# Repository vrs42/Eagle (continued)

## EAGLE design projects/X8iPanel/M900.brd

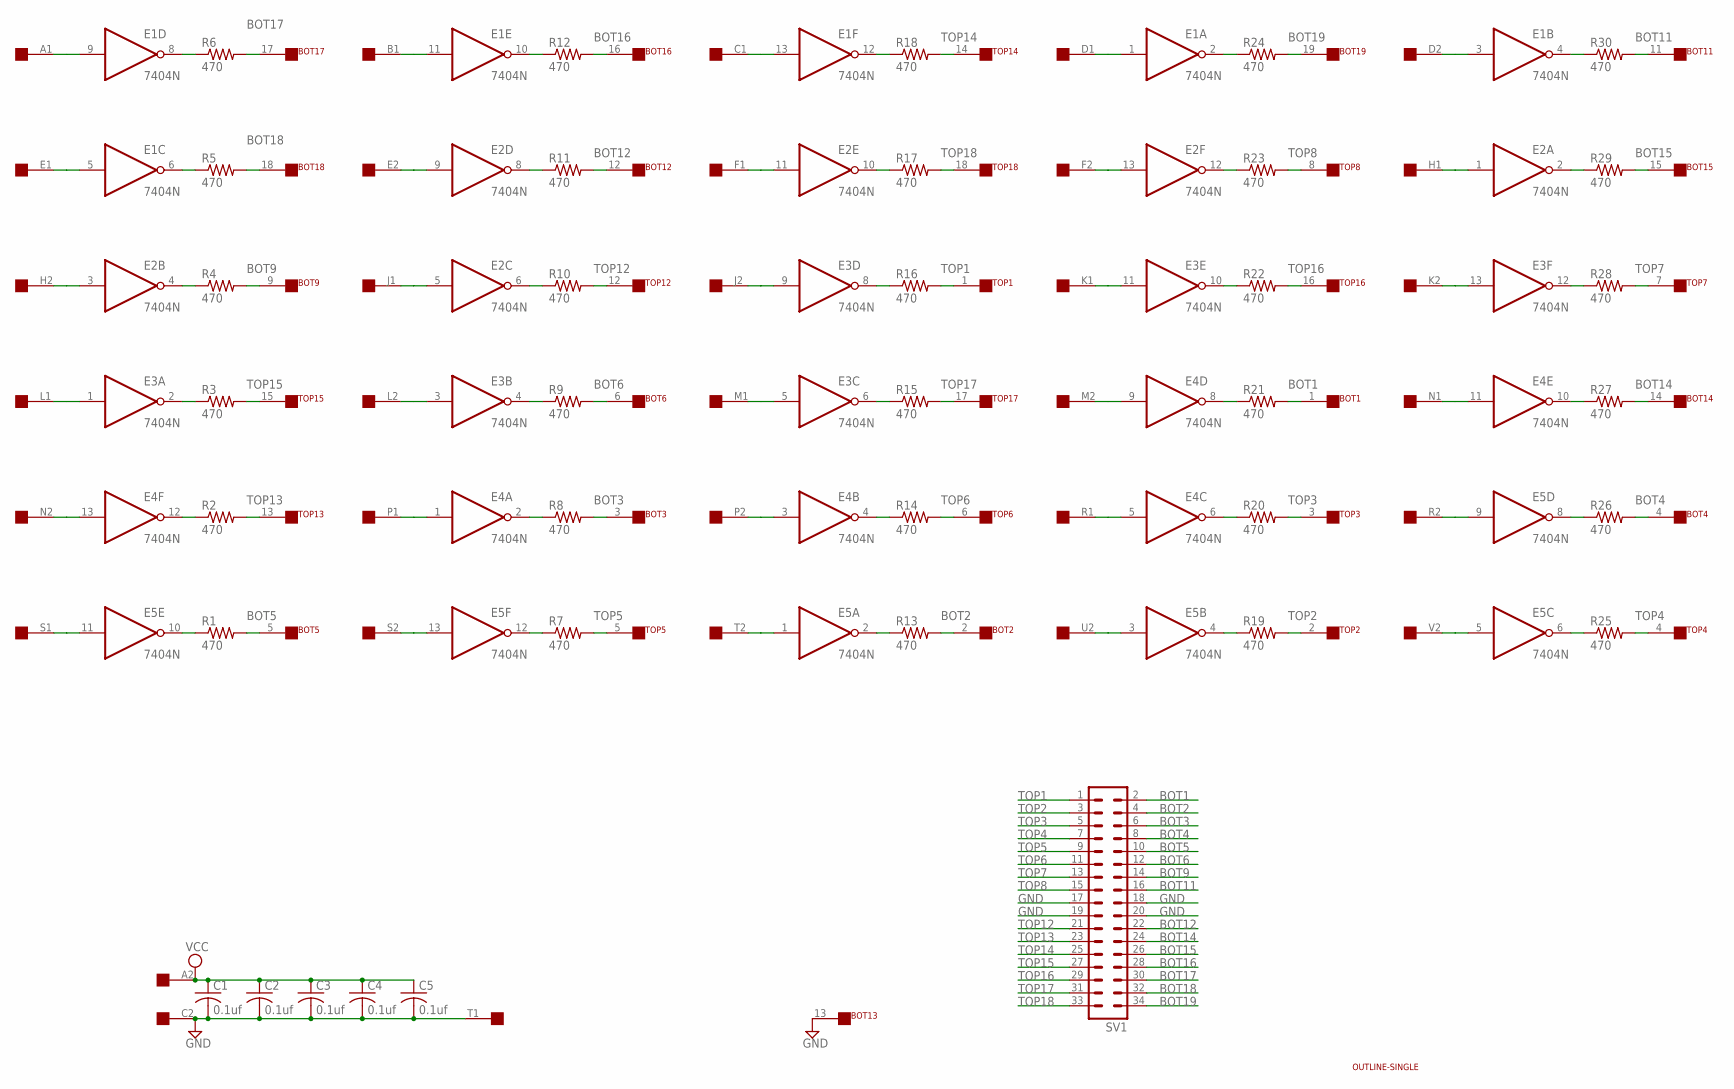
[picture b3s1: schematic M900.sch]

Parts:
BOT: FLEX19
C1, C2, C3, C4, C5: 0.1uf; C050-025X075
E1, E2, E3, E4, E5: 7404N; DIL14
EDGE: SINGLE; EDGE-CON2
R1, R2, R3, R4, R5, R6, R7, R8, R9, R10, R11, R12, R13, R14, R15, R16, R17, R18, R19, R20, R21, R22, R23, R24, R25, R26, R27, R28, R29, R30: 470; 0207/10
SV1: MA17-2
TOP: FLEX19
U$2: OUTLINE-SINGLE; SINGLE

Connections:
BOT1: BOT.1, R21.2, SV1.2
BOT2: BOT.2, R13.2, SV1.4
BOT3: BOT.3, R8.2, SV1.6
BOT4: BOT.4, R26.2, SV1.8
BOT5: BOT.5, R1.2, SV1.10
BOT6: BOT.6, R9.2, SV1.12
BOT9: BOT.9, R4.2, SV1.14
BOT11: BOT.11, R30.2, SV1.16
BOT12: BOT.12, R11.2, SV1.22
BOT14: BOT.14, R27.2, SV1.24
BOT15: BOT.15, R29.2, SV1.26
BOT16: BOT.16, R12.2, SV1.28
BOT17: BOT.17, R6.2, SV1.30
BOT18: BOT.18, R5.2, SV1.32
BOT19: BOT.19, R24.2, SV1.34
GND: BOT.13, C1.2, C2.2, C3.2, C4.2, C5.2, E1.7 (GND), E2.7 (GND), E3.7 (GND), E4.7 (GND), E5.7 (GND), EDGE.C2, EDGE.T1, SV1.17, SV1.18, SV1.19, SV1.20
unnamed: E1.9 (I), EDGE.A1
unnamed: E1.8 (O), R6.1
unnamed: E1.6 (O), R5.1
unnamed: E2.4 (O), R4.1
unnamed: E3.2 (O), R3.1
unnamed: E4.12 (O), R2.1
unnamed: E2.3 (I), EDGE.H2
unnamed: E5.11 (I), EDGE.S1
unnamed: E4.13 (I), EDGE.N2
unnamed: E3.1 (I), EDGE.L1
unnamed: E1.5 (I), EDGE.E1
unnamed: E4.1 (I), EDGE.P1
unnamed: E1.11 (I), EDGE.B1
unnamed: E2.9 (I), EDGE.E2
unnamed: E2.5 (I), EDGE.J1
unnamed: E3.3 (I), EDGE.L2
unnamed: E5.13 (I), EDGE.S2
unnamed: E4.2 (O), R8.1
unnamed: E3.4 (O), R9.1
unnamed: E2.6 (O), R10.1
unnamed: E2.8 (O), R11.1
unnamed: E1.10 (O), R12.1
unnamed: E5.12 (O), R7.1
unnamed: E5.10 (O), R1.1
unnamed: E4.3 (I), EDGE.P2
unnamed: E1.13 (I), EDGE.C1
unnamed: E2.11 (I), EDGE.F1
unnamed: E3.9 (I), EDGE.J2
unnamed: E3.5 (I), EDGE.M1
unnamed: E5.1 (I), EDGE.T2
unnamed: E5.2 (O), R13.1
unnamed: E4.4 (O), R14.1
unnamed: E3.6 (O), R15.1
unnamed: E3.8 (O), R16.1
unnamed: E1.12 (O), R18.1
unnamed: E2.10 (O), R17.1
unnamed: E5.4 (O), R19.1
unnamed: E4.6 (O), R20.1
unnamed: E4.8 (O), R21.1
unnamed: E3.10 (O), R22.1
unnamed: E2.12 (O), R23.1
unnamed: E1.2 (O), R24.1
unnamed: E4.5 (I), EDGE.R1
unnamed: E2.13 (I), EDGE.F2
unnamed: E3.11 (I), EDGE.K1
unnamed: E4.9 (I), EDGE.M2
unnamed: E5.3 (I), EDGE.U2
unnamed: E5.9 (I), EDGE.R2
unnamed: E1.1 (I), EDGE.D1
unnamed: E1.3 (I), EDGE.D2
unnamed: E2.1 (I), EDGE.H1
unnamed: E3.13 (I), EDGE.K2
unnamed: E4.11 (I), EDGE.N1
unnamed: E5.5 (I), EDGE.V2
unnamed: E5.6 (O), R25.1
unnamed: E5.8 (O), R26.1
unnamed: E4.10 (O), R27.1
unnamed: E3.12 (O), R28.1
unnamed: E2.2 (O), R29.1
unnamed: E1.4 (O), R30.1
TOP1: R16.2, SV1.1, TOP.1
TOP2: R19.2, SV1.3, TOP.2
TOP3: R20.2, SV1.5, TOP.3
TOP4: R25.2, SV1.7, TOP.4
TOP5: R7.2, SV1.9, TOP.5
TOP6: R14.2, SV1.11, TOP.6
TOP7: R28.2, SV1.13, TOP.7
TOP8: R23.2, SV1.15, TOP.8
TOP12: R10.2, SV1.21, TOP.12
TOP13: R2.2, SV1.23, TOP.13
TOP14: R18.2, SV1.25, TOP.14
TOP15: R3.2, SV1.27, TOP.15
TOP16: R22.2, SV1.29, TOP.16
TOP17: R15.2, SV1.31, TOP.17
TOP18: R17.2, SV1.33, TOP.18
VCC: C1.1, C2.1, C3.1, C4.1, C5.1, E1.14 (VCC), E2.14 (VCC), E3.14 (VCC), E4.14 (VCC), E5.14 (VCC), EDGE.A2

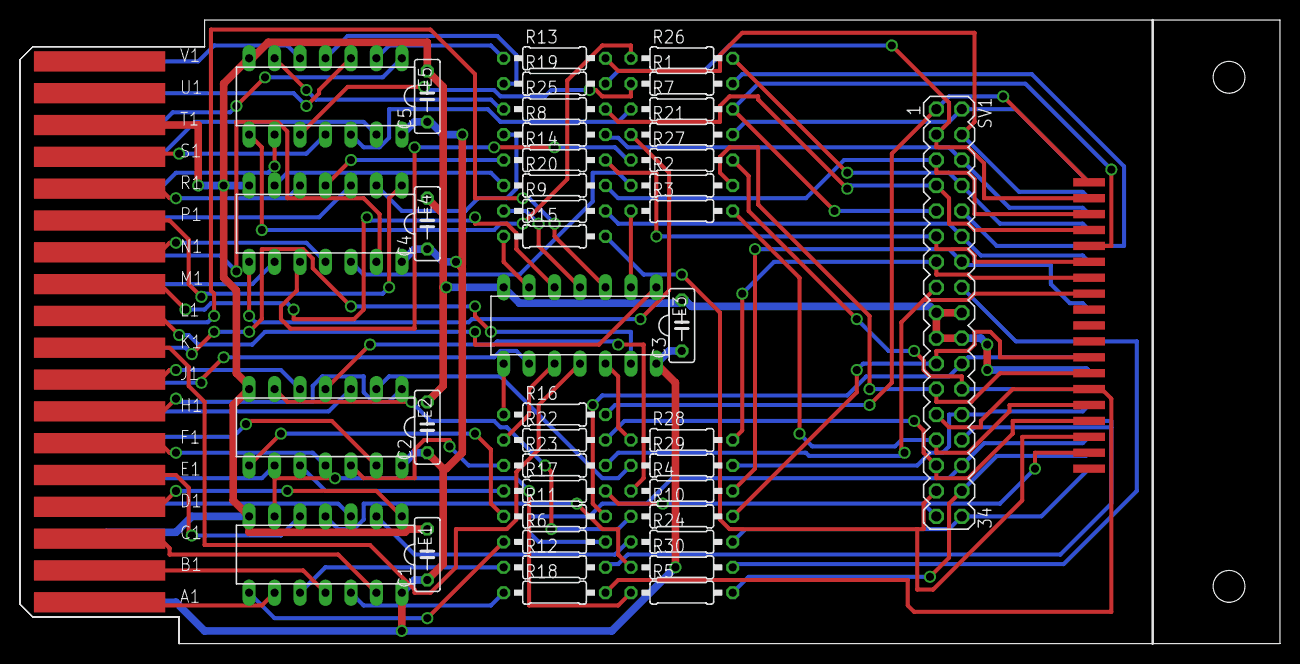
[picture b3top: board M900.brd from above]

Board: 2 copper layers, 125.7 x 62.2 mm, 45 parts (1 on the bottom side), 92 nets.

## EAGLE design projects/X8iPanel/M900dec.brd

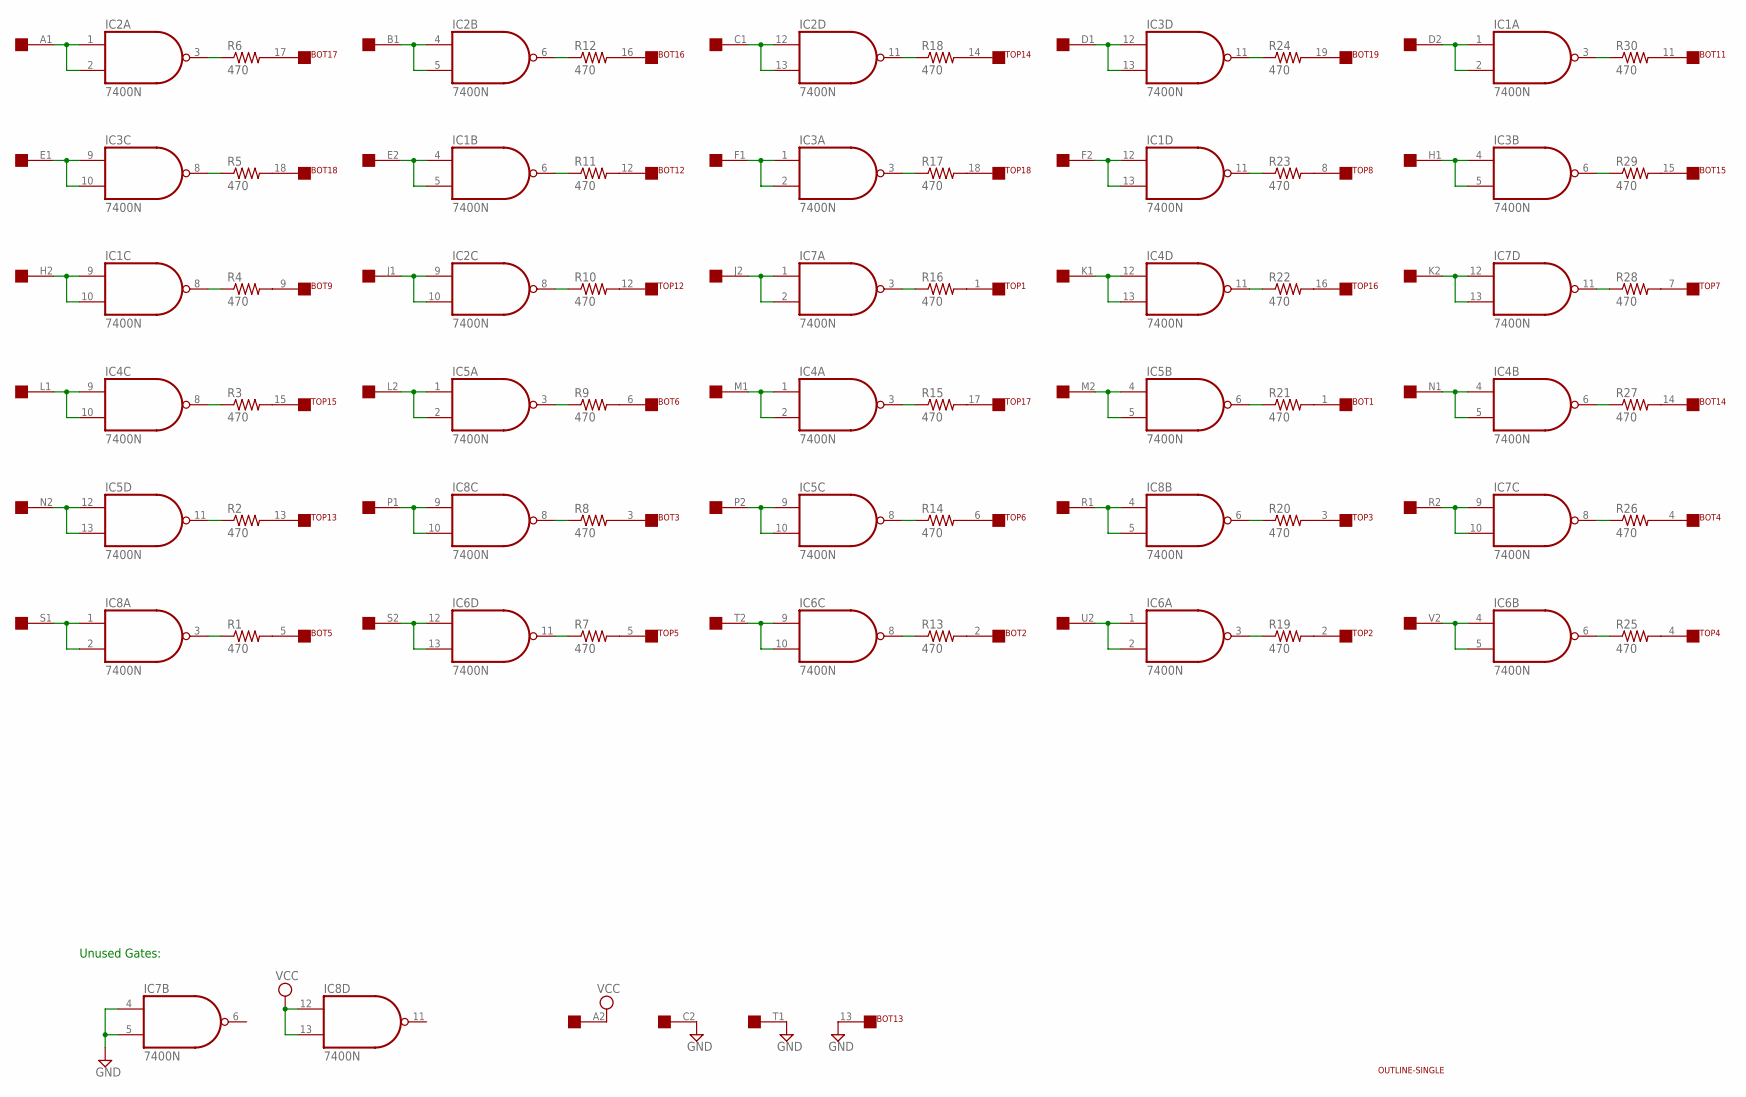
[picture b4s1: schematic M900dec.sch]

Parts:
BOT: FLEX19
EDGE: SINGLE; EDGE-CON2
IC1, IC2, IC3, IC4, IC5, IC6, IC7, IC8: 7400N; DIL14
R1, R2, R3, R4, R5, R6, R7, R8, R9, R10, R11, R12, R13, R14, R15, R16, R17, R18, R19, R20, R21, R22, R23, R24, R25, R26, R27, R28, R29, R30: 470; 0207/10
TOP: FLEX19
U$2: OUTLINE-SINGLE; SINGLE

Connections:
GND: BOT.13, EDGE.C2, EDGE.T1, IC1.7 (GND), IC2.7 (GND), IC3.7 (GND), IC4.7 (GND), IC5.7 (GND), IC6.7 (GND), IC7.4 (I0), IC7.5 (I1), IC7.7 (GND), IC8.7 (GND)
unnamed: EDGE.A1, IC2.1 (I0), IC2.2 (I1)
unnamed: IC2.3 (O), R6.1
unnamed: IC3.8 (O), R5.1
unnamed: IC1.8 (O), R4.1
unnamed: IC4.8 (O), R3.1
unnamed: IC5.11 (O), R2.1
unnamed: EDGE.H2, IC1.9 (I0), IC1.10 (I1)
unnamed: EDGE.S1, IC8.1 (I0), IC8.2 (I1)
unnamed: EDGE.N2, IC5.12 (I0), IC5.13 (I1)
unnamed: EDGE.L1, IC4.9 (I0), IC4.10 (I1)
unnamed: EDGE.E1, IC3.9 (I0), IC3.10 (I1)
unnamed: EDGE.P1, IC8.9 (I0), IC8.10 (I1)
unnamed: EDGE.B1, IC2.4 (I0), IC2.5 (I1)
unnamed: EDGE.E2, IC1.4 (I0), IC1.5 (I1)
unnamed: EDGE.J1, IC2.9 (I0), IC2.10 (I1)
unnamed: EDGE.L2, IC5.1 (I0), IC5.2 (I1)
unnamed: EDGE.S2, IC6.12 (I0), IC6.13 (I1)
unnamed: IC8.8 (O), R8.1
unnamed: IC5.3 (O), R9.1
unnamed: IC2.8 (O), R10.1
unnamed: IC1.6 (O), R11.1
unnamed: IC2.6 (O), R12.1
unnamed: IC6.11 (O), R7.1
unnamed: IC8.3 (O), R1.1
unnamed: EDGE.P2, IC5.9 (I0), IC5.10 (I1)
unnamed: EDGE.C1, IC2.12 (I0), IC2.13 (I1)
unnamed: EDGE.F1, IC3.1 (I0), IC3.2 (I1)
unnamed: EDGE.J2, IC7.1 (I0), IC7.2 (I1)
unnamed: EDGE.M1, IC4.1 (I0), IC4.2 (I1)
unnamed: EDGE.T2, IC6.9 (I0), IC6.10 (I1)
unnamed: IC6.8 (O), R13.1
unnamed: IC5.8 (O), R14.1
unnamed: IC4.3 (O), R15.1
unnamed: IC7.3 (O), R16.1
unnamed: IC2.11 (O), R18.1
unnamed: IC3.3 (O), R17.1
unnamed: IC6.3 (O), R19.1
unnamed: IC8.6 (O), R20.1
unnamed: IC5.6 (O), R21.1
unnamed: IC4.11 (O), R22.1
unnamed: IC1.11 (O), R23.1
unnamed: IC3.11 (O), R24.1
unnamed: EDGE.R1, IC8.4 (I0), IC8.5 (I1)
unnamed: EDGE.F2, IC1.12 (I0), IC1.13 (I1)
unnamed: EDGE.K1, IC4.12 (I0), IC4.13 (I1)
unnamed: EDGE.M2, IC5.4 (I0), IC5.5 (I1)
unnamed: EDGE.U2, IC6.1 (I0), IC6.2 (I1)
unnamed: EDGE.R2, IC7.9 (I0), IC7.10 (I1)
unnamed: EDGE.D1, IC3.12 (I0), IC3.13 (I1)
unnamed: EDGE.D2, IC1.1 (I0), IC1.2 (I1)
unnamed: EDGE.H1, IC3.4 (I0), IC3.5 (I1)
unnamed: EDGE.K2, IC7.12 (I0), IC7.13 (I1)
unnamed: EDGE.N1, IC4.4 (I0), IC4.5 (I1)
unnamed: EDGE.V2, IC6.4 (I0), IC6.5 (I1)
unnamed: IC6.6 (O), R25.1
unnamed: IC7.8 (O), R26.1
unnamed: IC4.6 (O), R27.1
unnamed: IC7.11 (O), R28.1
unnamed: IC3.6 (O), R29.1
unnamed: IC1.3 (O), R30.1
unnamed: R17.2, TOP.18
unnamed: R15.2, TOP.17
unnamed: R22.2, TOP.16
unnamed: R3.2, TOP.15
unnamed: R18.2, TOP.14
unnamed: R2.2, TOP.13
unnamed: R10.2, TOP.12
unnamed: R23.2, TOP.8
unnamed: R28.2, TOP.7
unnamed: R14.2, TOP.6
unnamed: R7.2, TOP.5
unnamed: R25.2, TOP.4
unnamed: R20.2, TOP.3
unnamed: R19.2, TOP.2
unnamed: R16.2, TOP.1
unnamed: BOT.15, R29.2
unnamed: BOT.3, R8.2
unnamed: BOT.1, R21.2
unnamed: BOT.2, R13.2
unnamed: BOT.4, R26.2
unnamed: BOT.5, R1.2
unnamed: BOT.19, R24.2
unnamed: BOT.18, R5.2
unnamed: BOT.17, R6.2
unnamed: BOT.16, R12.2
unnamed: BOT.14, R27.2
unnamed: BOT.12, R11.2
unnamed: BOT.9, R4.2
unnamed: BOT.6, R9.2
unnamed: BOT.11, R30.2
VCC: EDGE.A2, IC1.14 (VCC), IC2.14 (VCC), IC3.14 (VCC), IC4.14 (VCC), IC5.14 (VCC), IC6.14 (VCC), IC7.14 (VCC), IC8.12 (I0), IC8.13 (I1), IC8.14 (VCC)

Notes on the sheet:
Unused Gates:

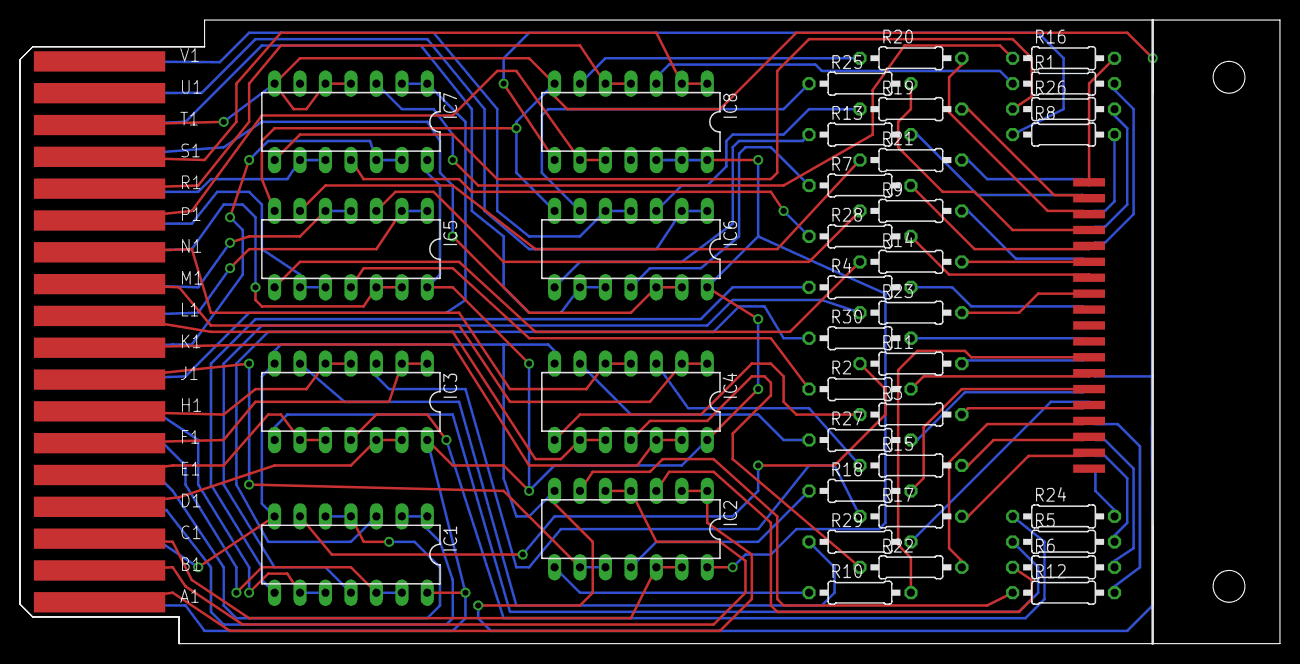
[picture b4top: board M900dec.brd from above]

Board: 2 copper layers, 125.7 x 62.2 mm, 42 parts (1 on the bottom side), 92 nets.

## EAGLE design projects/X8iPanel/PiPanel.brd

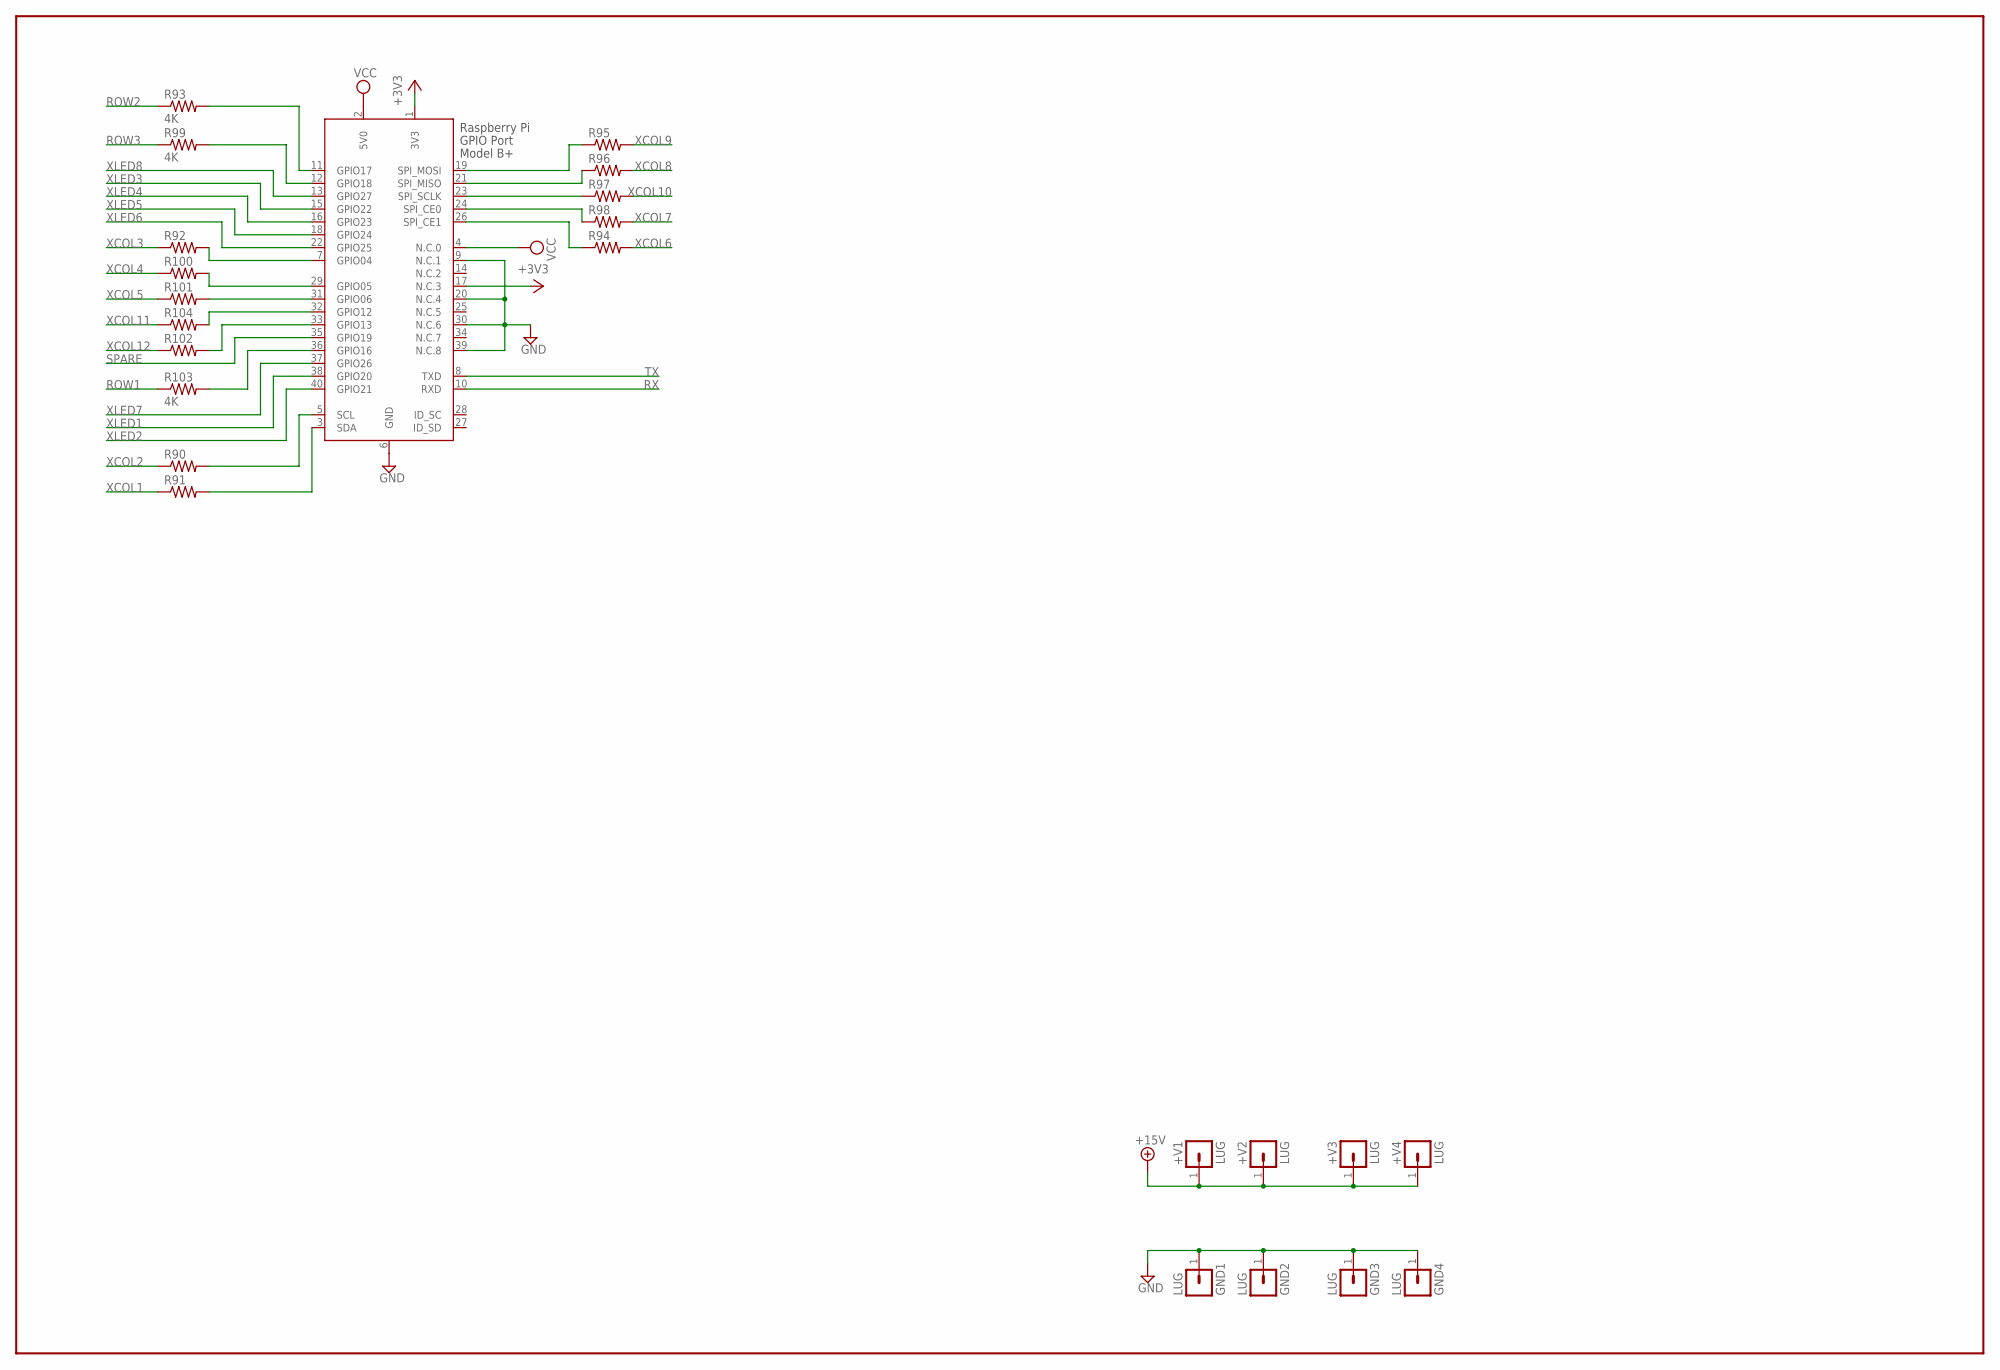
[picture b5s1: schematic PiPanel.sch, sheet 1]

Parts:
+V1, +V2, +V3, +V4: LUG; SPADELUG
GND1, GND2, GND3, GND4: LUG; SPADELUG
R90, R91, R92, R94, R95, R96, R97, R98, R100, R101, R102, R104: R-US_0207/10; 0207/10
R93, R99, R103: 4K; 0207/10
X1: RASPI_BOARD_B+_F; RASPI_BOARD_B+_FULL

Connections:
+3V3: X1.1 (3V3), X1.17 (N.C.3)
+15V: +V1.1, +V2.1, +V3.1, +V4.1
GND: GND1.1, GND2.1, GND3.1, GND4.1, X1.6 (GND), X1.9 (N.C.1), X1.20 (N.C.4), X1.30 (N.C.6), X1.39 (N.C.8); also elsewhere on the board
unnamed: R91.2, X1.3 (SDA)
unnamed: R90.2, X1.5 (SCL)
unnamed: R92.2, X1.7 (GPIO04)
unnamed: R93.2, X1.11 (GPIO17)
unnamed: R94.1, X1.26 (SPI_CE1)
unnamed: R95.1, X1.19 (SPI_MOSI)
unnamed: R96.1, X1.21 (SPI_MISO)
unnamed: R97.1, X1.23 (SPI_SCLK)
unnamed: R98.1, X1.24 (SPI_CE0)
unnamed: R99.2, X1.12 (GPIO18)
unnamed: R104.2, X1.32 (GPIO12)
unnamed: R102.2, X1.33 (GPIO13)
unnamed: R100.2, X1.29 (GPIO05)
unnamed: R101.2, X1.31 (GPIO06)
unnamed: R103.2, X1.36 (GPIO16)
ROW1: R103.1
ROW2: R93.1
ROW3: R99.1
RX: X1.10 (RXD)
SPARE: X1.35 (GPIO19)
TX: X1.8 (TXD)
VCC: X1.2 (5V0), X1.4 (N.C.0); also elsewhere on the board
XCOL1: R91.1; also elsewhere on the board
XCOL2: R90.1; also elsewhere on the board
XCOL3: R92.1; also elsewhere on the board
XCOL4: R100.1; also elsewhere on the board
XCOL5: R101.1; also elsewhere on the board
XCOL6: R94.2; also elsewhere on the board
XCOL7: R98.2; also elsewhere on the board
XCOL8: R96.2; also elsewhere on the board
XCOL9: R95.2; also elsewhere on the board
XCOL10: R97.2; also elsewhere on the board
XCOL11: R104.1; also elsewhere on the board
XCOL12: R102.1; also elsewhere on the board
XLED1: X1.38 (GPIO20); also elsewhere on the board
XLED2: X1.40 (GPIO21); also elsewhere on the board
XLED3: X1.15 (GPIO22); also elsewhere on the board
XLED4: X1.16 (GPIO23); also elsewhere on the board
XLED5: X1.18 (GPIO24); also elsewhere on the board
XLED6: X1.22 (GPIO25); also elsewhere on the board
XLED7: X1.37 (GPIO26); also elsewhere on the board
XLED8: X1.13 (GPIO27); also elsewhere on the board

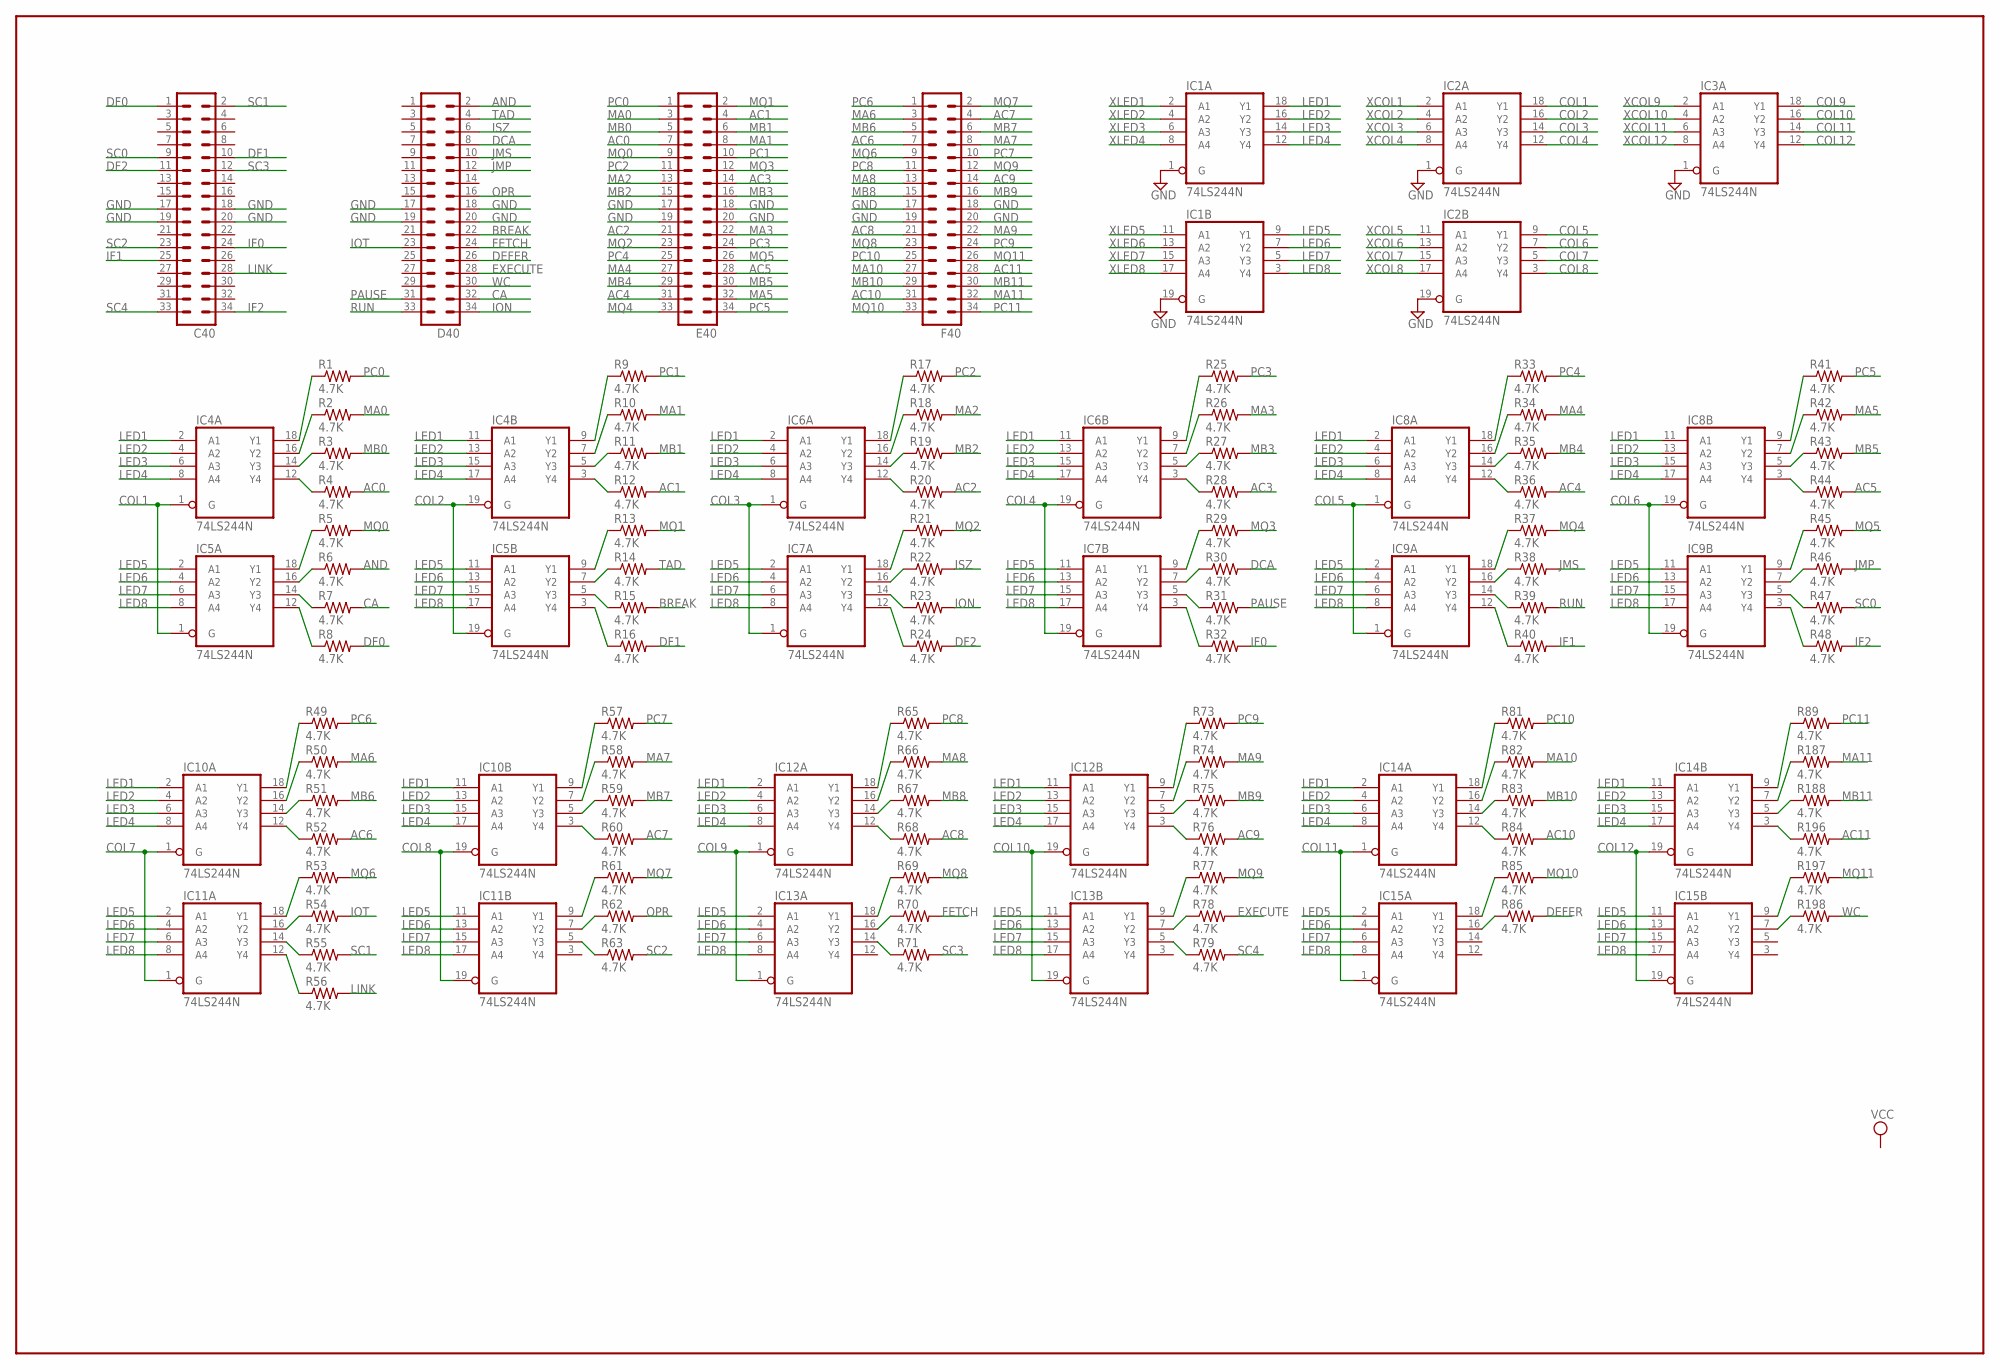
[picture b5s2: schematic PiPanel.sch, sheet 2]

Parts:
C40: MA17-2
D40: MA17-2
E40: MA17-2
F40: MA17-2
IC1, IC2, IC3, IC4, IC5, IC6, IC7, IC8, IC9, IC10, IC11, IC12, IC13, IC14, IC15: 74LS244N; DIL20
R1, R2, R3, R4, R5, R6, R7, R8, R9, R10, R11, R12, R13, R14, R15, R16, R17, R18, R19, R20, R21, R22, R23, R24, R25, R26, R27, R28, R29, R30, R31, R32, R33, R34, R35, R36, R37, R38, R39, R40, R41, R42, R43, R44, R45, R46, R47, R48, R49, R50, R51, R52, R53, R54, R55, R56, R57, R58, R59, R60, R61, R62, R63, R65, R66, R67, R68, R69, R70, R71, R73, R74, R75, R76, R77, R78, R79, R81, R82, R83, R84, R85, R86, R89, R187, R188, R196, R197, R198: 4.7K; 0207/10

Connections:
AC0: E40.7, R4.2
AC1: E40.4, R12.2
AC2: E40.21, R20.2
AC3: E40.14, R28.2
AC4: E40.31, R36.2
AC5: E40.28, R44.2
AC6: F40.7, R52.2
AC7: F40.4, R60.2
AC8: F40.21, R68.2
AC9: F40.14, R76.2
AC10: F40.31, R84.2
AC11: F40.28, R196.2
AND: D40.2, R6.2
BREAK: D40.22, R15.2
CA: D40.32, R7.2
COL1: IC2.18 (Y1), IC4.1 (G), IC5.1 (G)
COL2: IC2.16 (Y2), IC4.19 (G), IC5.19 (G)
COL3: IC2.14 (Y3), IC6.1 (G), IC7.1 (G)
COL4: IC2.12 (Y4), IC6.19 (G), IC7.19 (G)
COL5: IC2.9 (Y1), IC8.1 (G), IC9.1 (G)
COL6: IC2.7 (Y2), IC8.19 (G), IC9.19 (G)
COL7: IC2.5 (Y3), IC10.1 (G), IC11.1 (G)
COL8: IC2.3 (Y4), IC10.19 (G), IC11.19 (G)
COL9: IC3.18 (Y1), IC12.1 (G), IC13.1 (G)
COL10: IC3.16 (Y2), IC12.19 (G), IC13.19 (G)
COL11: IC3.14 (Y3), IC14.1 (G), IC15.1 (G)
COL12: IC3.12 (Y4), IC14.19 (G), IC15.19 (G)
DCA: D40.8, R30.2
DEFER: D40.26, R86.2
DF0: C40.1, R8.2
DF1: C40.10, R16.2
DF2: C40.11, R24.2
EXECUTE: D40.28, R78.2
FETCH: D40.24, R70.2
GND: C40.17, C40.18, C40.19, C40.20, D40.17, D40.18, D40.19, D40.20, E40.17, E40.18, E40.19, E40.20, F40.17, F40.18, F40.19, F40.20, IC1.1 (G), IC1.10 (GND), IC1.19 (G), IC2.1 (G), IC2.10 (GND), IC2.19 (G), IC3.1 (G), IC3.10 (GND), IC4.10 (GND), IC5.10 (GND), IC6.10 (GND), IC7.10 (GND), IC8.10 (GND), IC9.10 (GND), IC10.10 (GND), IC11.10 (GND), IC12.10 (GND), IC13.10 (GND), IC14.10 (GND), IC15.10 (GND); also elsewhere on the board
IF0: C40.24, R32.2
IF1: C40.25, R40.2
IF2: C40.34, R48.2
ION: D40.34, R23.2
IOT: D40.23, R54.2
ISZ: D40.6, R22.2
JMP: D40.12, R46.2
JMS: D40.10, R38.2
LED1: IC1.18 (Y1), IC4.2 (A1), IC4.11 (A1), IC6.2 (A1), IC6.11 (A1), IC8.2 (A1), IC8.11 (A1), IC10.2 (A1), IC10.11 (A1), IC12.2 (A1), IC12.11 (A1), IC14.2 (A1), IC14.11 (A1)
LED2: IC1.16 (Y2), IC4.4 (A2), IC4.13 (A2), IC6.4 (A2), IC6.13 (A2), IC8.4 (A2), IC8.13 (A2), IC10.4 (A2), IC10.13 (A2), IC12.4 (A2), IC12.13 (A2), IC14.4 (A2), IC14.13 (A2)
LED3: IC1.14 (Y3), IC4.6 (A3), IC4.15 (A3), IC6.6 (A3), IC6.15 (A3), IC8.6 (A3), IC8.15 (A3), IC10.6 (A3), IC10.15 (A3), IC12.6 (A3), IC12.15 (A3), IC14.6 (A3), IC14.15 (A3)
LED4: IC1.12 (Y4), IC4.8 (A4), IC4.17 (A4), IC6.8 (A4), IC6.17 (A4), IC8.8 (A4), IC8.17 (A4), IC10.8 (A4), IC10.17 (A4), IC12.8 (A4), IC12.17 (A4), IC14.8 (A4), IC14.17 (A4)
LED5: IC1.9 (Y1), IC5.2 (A1), IC5.11 (A1), IC7.2 (A1), IC7.11 (A1), IC9.2 (A1), IC9.11 (A1), IC11.2 (A1), IC11.11 (A1), IC13.2 (A1), IC13.11 (A1), IC15.2 (A1), IC15.11 (A1)
LED6: IC1.7 (Y2), IC5.4 (A2), IC5.13 (A2), IC7.4 (A2), IC7.13 (A2), IC9.4 (A2), IC9.13 (A2), IC11.4 (A2), IC11.13 (A2), IC13.4 (A2), IC13.13 (A2), IC15.4 (A2), IC15.13 (A2)
LED7: IC1.5 (Y3), IC5.6 (A3), IC5.15 (A3), IC7.6 (A3), IC7.15 (A3), IC9.6 (A3), IC9.15 (A3), IC11.6 (A3), IC11.15 (A3), IC13.6 (A3), IC13.15 (A3), IC15.6 (A3), IC15.15 (A3)
LED8: IC1.3 (Y4), IC5.8 (A4), IC5.17 (A4), IC7.8 (A4), IC7.17 (A4), IC9.8 (A4), IC9.17 (A4), IC11.8 (A4), IC11.17 (A4), IC13.8 (A4), IC13.17 (A4), IC15.8 (A4), IC15.17 (A4)
LINK: C40.28, R56.2
MA0: E40.3, R2.2
MA1: E40.8, R10.2
MA2: E40.13, R18.2
MA3: E40.22, R26.2
MA4: E40.27, R34.2
MA5: E40.32, R42.2
MA6: F40.3, R50.2
MA7: F40.8, R58.2
MA8: F40.13, R66.2
MA9: F40.22, R74.2
MA10: F40.27, R82.2
MA11: F40.32, R187.2
MB0: E40.5, R3.2
MB1: E40.6, R11.2
MB2: E40.15, R19.2
MB3: E40.16, R27.2
MB4: E40.29, R35.2
MB5: E40.30, R43.2
MB6: F40.5, R51.2
MB7: F40.6, R59.2
MB8: F40.15, R67.2
MB9: F40.16, R75.2
MB10: F40.29, R83.2
MB11: F40.30, R188.2
MQ0: E40.9, R5.2
MQ1: E40.2, R13.2
MQ2: E40.23, R21.2
MQ3: E40.12, R29.2
MQ4: E40.33, R37.2
MQ5: E40.26, R45.2
MQ6: F40.9, R53.2
MQ7: F40.2, R61.2
MQ8: F40.23, R69.2
MQ9: F40.12, R77.2
MQ10: F40.33, R85.2
MQ11: F40.26, R197.2
unnamed: IC4.18 (Y1), R1.1
unnamed: IC4.12 (Y4), R4.1
unnamed: IC4.14 (Y3), R3.1
unnamed: IC4.16 (Y2), R2.1
unnamed: IC5.18 (Y1), R5.1
unnamed: IC5.16 (Y2), R6.1
unnamed: IC5.14 (Y3), R7.1
unnamed: IC5.12 (Y4), R8.1
unnamed: IC4.9 (Y1), R9.1
unnamed: IC4.3 (Y4), R12.1
unnamed: IC4.5 (Y3), R11.1
unnamed: IC4.7 (Y2), R10.1
unnamed: IC5.9 (Y1), R13.1
unnamed: IC5.7 (Y2), R14.1
unnamed: IC5.5 (Y3), R15.1
unnamed: IC5.3 (Y4), R16.1
unnamed: IC6.18 (Y1), R17.1
unnamed: IC6.12 (Y4), R20.1
unnamed: IC6.14 (Y3), R19.1
unnamed: IC6.16 (Y2), R18.1
unnamed: IC7.18 (Y1), R21.1
unnamed: IC7.16 (Y2), R22.1
unnamed: IC7.14 (Y3), R23.1
unnamed: IC7.12 (Y4), R24.1
unnamed: IC6.9 (Y1), R25.1
unnamed: IC6.3 (Y4), R28.1
unnamed: IC6.5 (Y3), R27.1
unnamed: IC6.7 (Y2), R26.1
unnamed: IC7.9 (Y1), R29.1
unnamed: IC7.7 (Y2), R30.1
unnamed: IC7.5 (Y3), R31.1
unnamed: IC7.3 (Y4), R32.1
unnamed: IC8.18 (Y1), R33.1
unnamed: IC8.12 (Y4), R36.1
unnamed: IC8.14 (Y3), R35.1
unnamed: IC8.16 (Y2), R34.1
unnamed: IC9.18 (Y1), R37.1
unnamed: IC9.16 (Y2), R38.1
unnamed: IC9.14 (Y3), R39.1
unnamed: IC9.12 (Y4), R40.1
unnamed: IC8.9 (Y1), R41.1
unnamed: IC8.3 (Y4), R44.1
unnamed: IC8.5 (Y3), R43.1
unnamed: IC8.7 (Y2), R42.1
unnamed: IC9.9 (Y1), R45.1
unnamed: IC9.7 (Y2), R46.1
unnamed: IC9.5 (Y3), R47.1
unnamed: IC9.3 (Y4), R48.1
unnamed: IC10.18 (Y1), R49.1
unnamed: IC10.12 (Y4), R52.1
unnamed: IC10.14 (Y3), R51.1
unnamed: IC10.16 (Y2), R50.1
unnamed: IC11.18 (Y1), R53.1
unnamed: IC11.16 (Y2), R54.1
unnamed: IC11.14 (Y3), R55.1
unnamed: IC11.12 (Y4), R56.1
unnamed: IC10.9 (Y1), R57.1
unnamed: IC10.3 (Y4), R60.1
unnamed: IC10.5 (Y3), R59.1
unnamed: IC10.7 (Y2), R58.1
unnamed: IC11.9 (Y1), R61.1
unnamed: IC11.7 (Y2), R62.1
unnamed: IC11.5 (Y3), R63.1
unnamed: IC12.18 (Y1), R65.1
unnamed: IC12.12 (Y4), R68.1
unnamed: IC12.14 (Y3), R67.1
unnamed: IC12.16 (Y2), R66.1
unnamed: IC13.18 (Y1), R69.1
unnamed: IC13.16 (Y2), R70.1
unnamed: IC13.14 (Y3), R71.1
unnamed: IC12.9 (Y1), R73.1
unnamed: IC12.3 (Y4), R76.1
unnamed: IC12.5 (Y3), R75.1
unnamed: IC12.7 (Y2), R74.1
unnamed: IC13.9 (Y1), R77.1
unnamed: IC13.7 (Y2), R78.1
unnamed: IC13.5 (Y3), R79.1
unnamed: IC14.18 (Y1), R81.1
unnamed: IC14.12 (Y4), R84.1
unnamed: IC14.14 (Y3), R83.1
unnamed: IC14.16 (Y2), R82.1
unnamed: IC15.18 (Y1), R85.1
unnamed: IC15.16 (Y2), R86.1
unnamed: IC14.9 (Y1), R89.1
unnamed: IC14.3 (Y4), R196.1
unnamed: IC14.5 (Y3), R188.1
unnamed: IC14.7 (Y2), R187.1
unnamed: IC15.9 (Y1), R197.1
unnamed: IC15.7 (Y2), R198.1
OPR: D40.16, R62.2
PAUSE: D40.31, R31.2
PC0: E40.1, R1.2
PC1: E40.10, R9.2
PC2: E40.11, R17.2
PC3: E40.24, R25.2
PC4: E40.25, R33.2
PC5: E40.34, R41.2
PC6: F40.1, R49.2
PC7: F40.10, R57.2
PC8: F40.11, R65.2
PC9: F40.24, R73.2
PC10: F40.25, R81.2
PC11: F40.34, R89.2
RUN: D40.33, R39.2
SC0: C40.9, R47.2
SC1: C40.2, R55.2
SC2: C40.23, R63.2
SC3: C40.12, R71.2
SC4: C40.33, R79.2
TAD: D40.4, R14.2
VCC: IC1.20 (VCC), IC2.20 (VCC), IC3.20 (VCC), IC4.20 (VCC), IC5.20 (VCC), IC6.20 (VCC), IC7.20 (VCC), IC8.20 (VCC), IC9.20 (VCC), IC10.20 (VCC), IC11.20 (VCC), IC12.20 (VCC), IC13.20 (VCC), IC14.20 (VCC), IC15.20 (VCC); also elsewhere on the board
WC: D40.30, R198.2
XCOL1: IC2.2 (A1); also elsewhere on the board
XCOL2: IC2.4 (A2); also elsewhere on the board
XCOL3: IC2.6 (A3); also elsewhere on the board
XCOL4: IC2.8 (A4); also elsewhere on the board
XCOL5: IC2.11 (A1); also elsewhere on the board
XCOL6: IC2.13 (A2); also elsewhere on the board
XCOL7: IC2.15 (A3); also elsewhere on the board
XCOL8: IC2.17 (A4); also elsewhere on the board
XCOL9: IC3.2 (A1); also elsewhere on the board
XCOL10: IC3.4 (A2); also elsewhere on the board
XCOL11: IC3.6 (A3); also elsewhere on the board
XCOL12: IC3.8 (A4); also elsewhere on the board
XLED1: IC1.2 (A1); also elsewhere on the board
XLED2: IC1.4 (A2); also elsewhere on the board
XLED3: IC1.6 (A3); also elsewhere on the board
XLED4: IC1.8 (A4); also elsewhere on the board
XLED5: IC1.11 (A1); also elsewhere on the board
XLED6: IC1.13 (A2); also elsewhere on the board
XLED7: IC1.15 (A3); also elsewhere on the board
XLED8: IC1.17 (A4); also elsewhere on the board

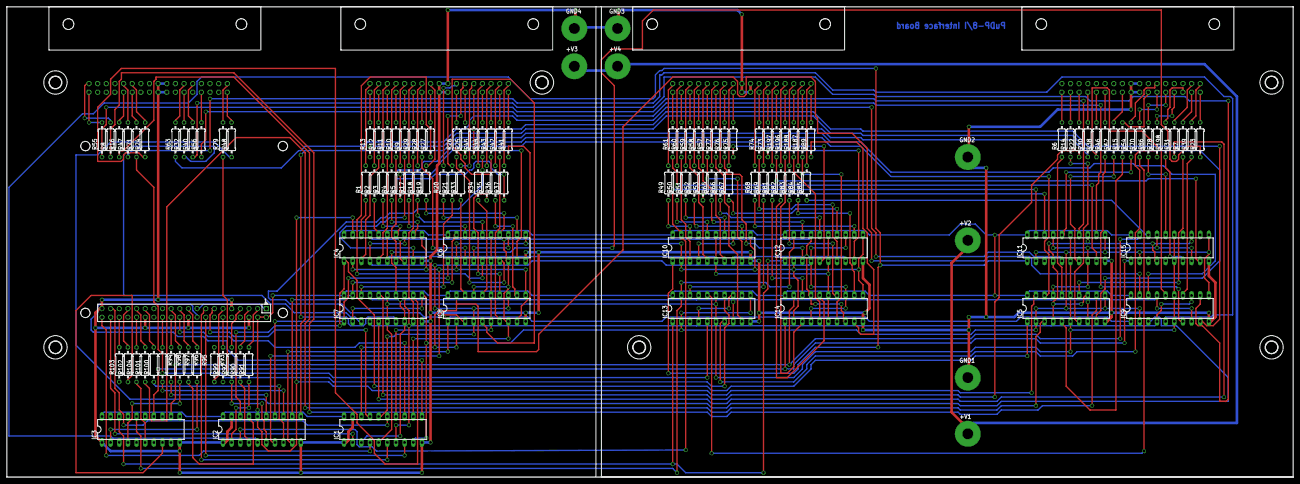
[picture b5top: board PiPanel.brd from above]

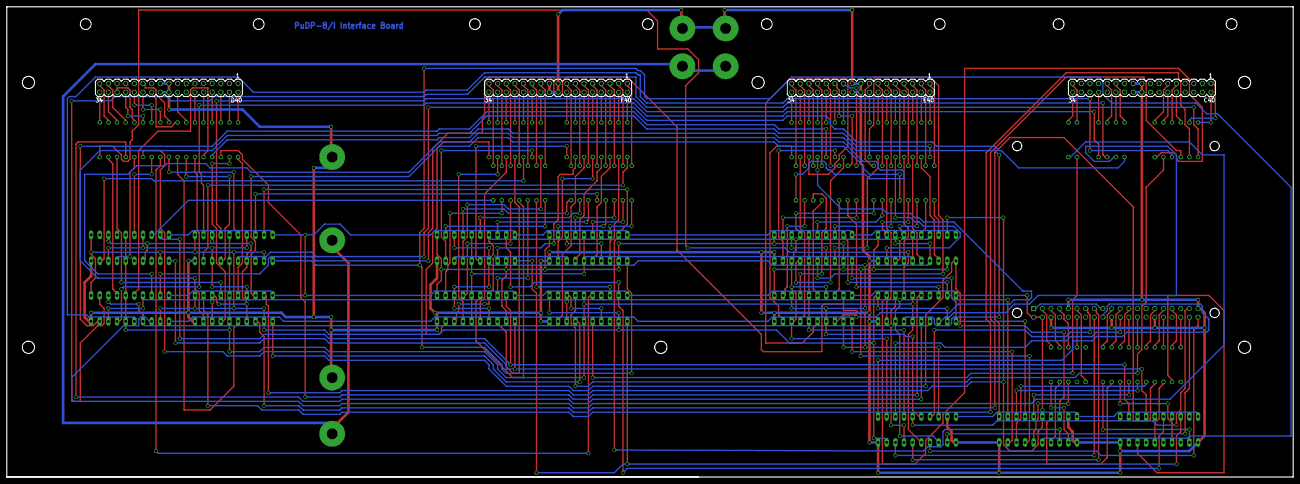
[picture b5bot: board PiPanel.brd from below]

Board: 2 copper layers, 377.8 x 138.1 mm, 142 parts (4 on the bottom side), 237 nets.

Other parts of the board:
U$1, U$2, U$3, U$4: STRAIN-RELIEF
U$5, U$6, U$7, U$8, U$9, U$11: 3,6
